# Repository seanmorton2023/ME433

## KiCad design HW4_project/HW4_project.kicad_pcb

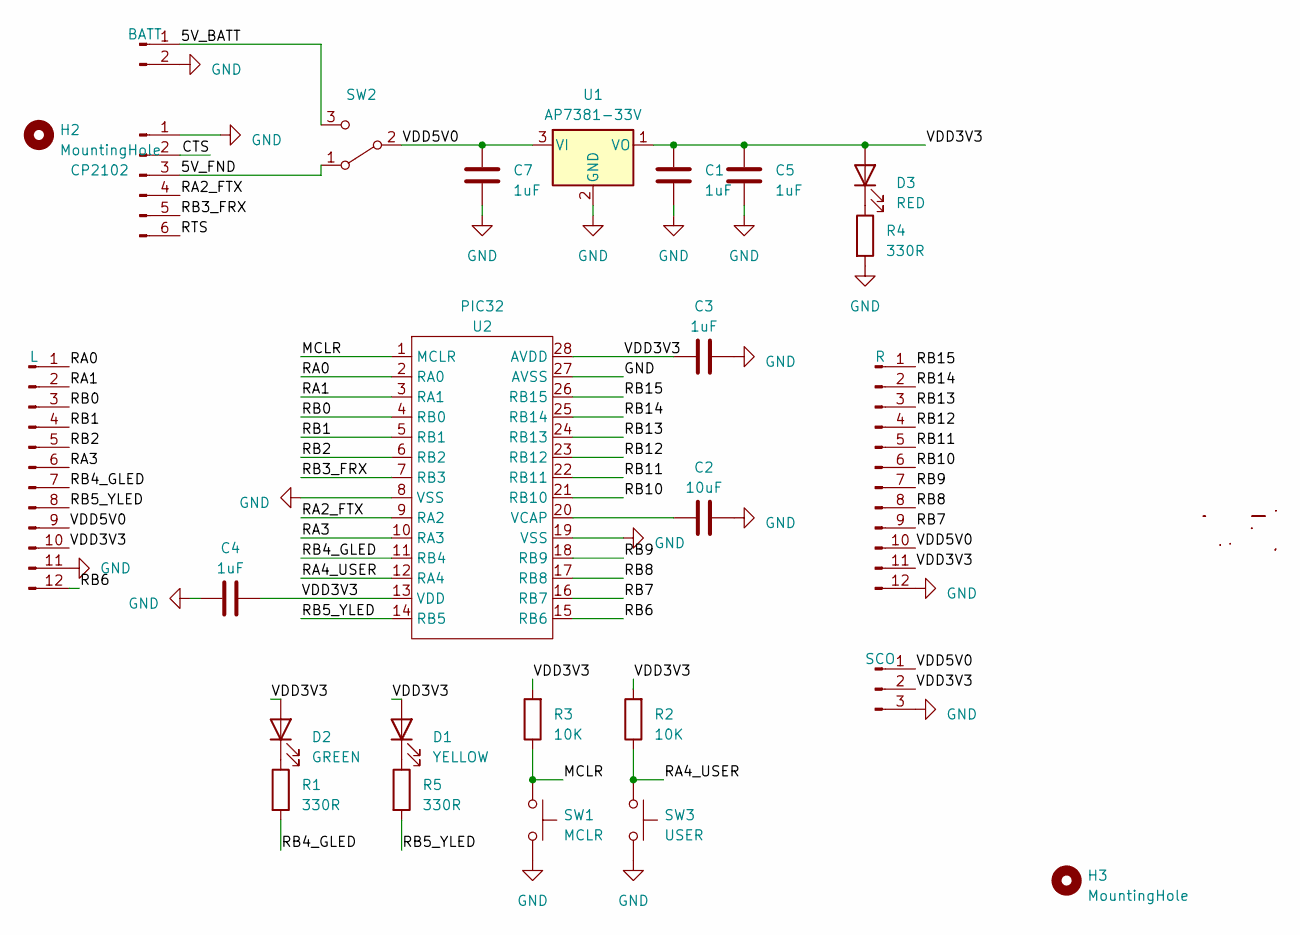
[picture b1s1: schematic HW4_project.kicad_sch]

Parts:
C1, C3, C4, C5, C7: 1uF; C_Disc_D4.3mm_W1.9mm_P5.00mm
C2: 10uF; C_Disc_D3.4mm_W2.1mm_P2.50mm
D1: YELLOW; LED_D4.0mm
D2: GREEN; LED_D4.0mm
D3: RED; LED_D4.0mm
H2, H3: MountingHole; MountingHole_3.2mm_M3_Pad
J1: CP2102; PinHeader_1x06_P2.54mm_Vertical
J2: BATT; PinHeader_1x02_P2.54mm_Vertical
J3: L; PinHeader_1x12_P2.54mm_Vertical
J4: R; PinHeader_1x12_P2.54mm_Vertical
J5: SCO; PinHeader_1x03_P2.54mm_Vertical
R1, R4, R5: 330R; R_Axial_DIN0207_L6.3mm_D2.5mm_P7.62mm_Horizontal
R2, R3: 10K; R_Axial_DIN0207_L6.3mm_D2.5mm_P7.62mm_Horizontal
SW1: MCLR; BTN_2pin_square
SW2: SW_SPDT; EG1218 switch
SW3: USER; BTN_2pin_square
U1: AP7381-33V; TO-92_Inline_Wide
U2: PIC32; DIP-28_W7.62mm_Socket_LongPads

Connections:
/5V_BATT: J2.1, SW2.3 (C)
/5V_FND: J1.3, SW2.1 (A)
/CTS: J1.2
/MCLR: R3.1, SW1.1, U2.1 (MCLR)
/RA0: J3.1, U2.2 (RA0)
/RA1: J3.2, U2.3 (RA1)
/RA2_FTX: J1.4, U2.9 (RA2)
/RA3: J3.6, U2.10 (RA3)
/RA4_USER: R2.1, SW3.1, U2.12 (RA4)
/RB0: J3.3, U2.4 (RB0)
/RB1: J3.4, U2.5 (RB1)
/RB2: J3.5, U2.6 (RB2)
/RB3_FRX: J1.5, U2.7 (RB3)
/RB4_GLED: J3.7, R1.2, U2.11 (RB4)
/RB5_YLED: J3.8, R5.2, U2.14 (RB5)
/RB6: J3.12, U2.15 (RB6)
/RB7: J4.9, U2.16 (RB7)
/RB8: J4.8, U2.17 (RB8)
/RB9: J4.7, U2.18 (RB9)
/RB10: J4.6, U2.21 (RB10)
/RB11: J4.5, U2.22 (RB11)
/RB12: J4.4, U2.23 (RB12)
/RB13: J4.3, U2.24 (RB13)
/RB14: J4.2, U2.25 (RB14)
/RB15: J4.1, U2.26 (RB15)
/RTS: J1.6
/VDD3V3: C1.1, C3.1, C4.2, C5.1, D1.2 (A), D2.2 (A), D3.2 (A), J3.10, J4.11, J5.2, R2.2, R3.2, U1.1 (VO), U2.13 (VDD), U2.28 (AVDD)
/VDD5V0: C7.1, J3.9, J4.10, J5.1, SW2.2 (B), U1.3 (VI)
GND: C1.2, C2.2, C3.2, C4.1, C5.2, C7.2, H2.1, H3.1, J1.1, J2.2, J3.11, J4.12, J5.3, R4.2, SW1.2, SW3.2, U1.2 (GND), U2.8 (VSS), U2.19 (VSS), U2.27 (AVSS)
unnamed: D1.1 (K), R5.1
unnamed: D2.1 (K), R1.1
unnamed: D3.1 (K), R4.1
unnamed: C2.1, U2.20 (VCAP)

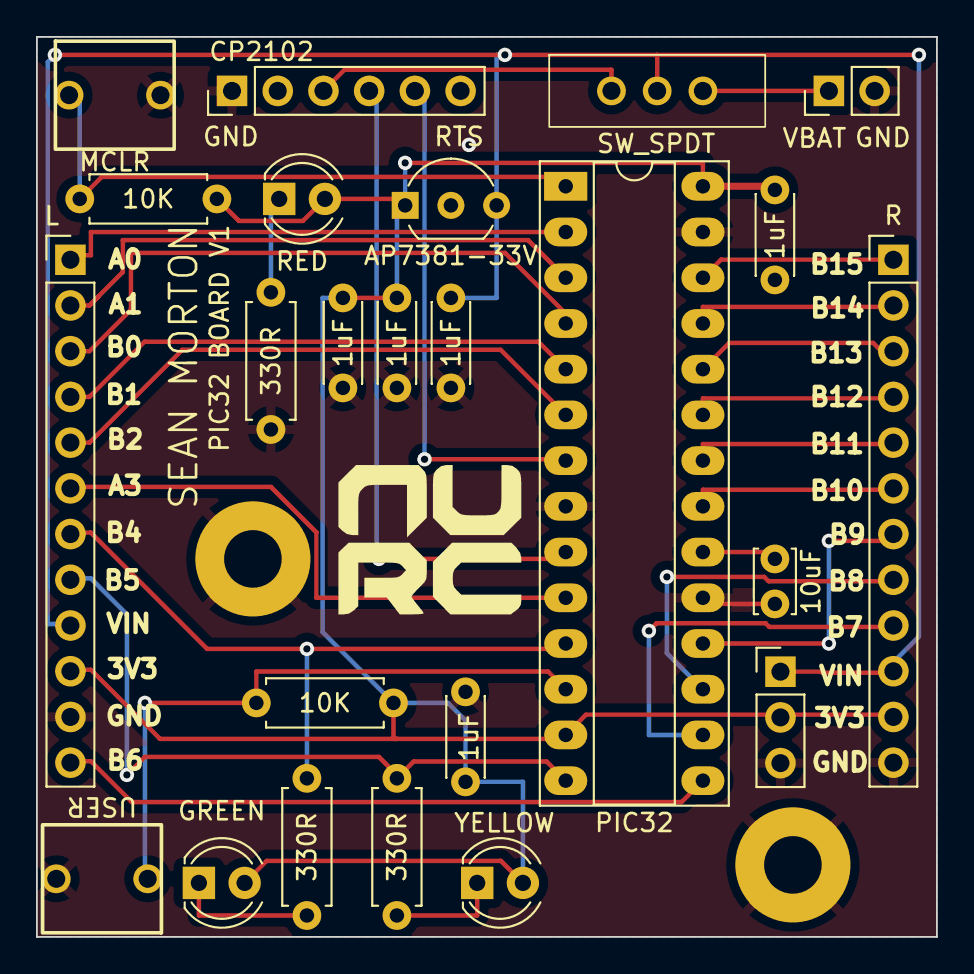
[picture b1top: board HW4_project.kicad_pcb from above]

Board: 2 copper layers, 50.0 x 50.0 mm, 26 parts (0 on the bottom side), 31 nets.

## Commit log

2023-04-01 HW2: started sample project
2023-04-04 HW2 submission
    pics and videos are under hw2.x/media
2023-04-04 HW2 media
    ...since it's in the requirements for this class, it's gonna be in the repo. except videos - those get submitted to Canvas
2023-04-06 HW3: added code
    code currently sends 1 sine wave every time button is pressed; viewed it on Arduino serial plotter
2023-04-06 HW3 submission
    successfully plots a sine wave of amplitude 1.65V and midpoint 1.65V
2023-04-13 HW4 + HW5 init
    - make first draft of PCB design for HW4
    - initialized HW5 project
2023-04-16 HW5: added files
    started work on the SPI DAC code
2023-04-16 HW5: 1st draft code
    covers all the bases, but is untested. test a little bit at a time
2023-04-19 Created HW6; edited HW5
    changed HW5 SPI initialization functions to choose pins for SDO, SDI, CS
2023-04-19 file organization
2023-04-20 init HW7; add HW6 I2C; modify HW5
    see Sarah's format for how she did a triangle wave in this commit
2023-04-20 HW5: sin and tri waves work
    had to fix bit-shifting and redefine my triangle wave, but both show up pretty clearly at low freqs. next up is to have both show up on the 2 output channels
2023-04-20 HW5 submission
    fixed SPI baud rate; signal now shows clean triangle and sine waves at the right frequencies
2023-04-25 HW6: got I2C writes working
    had a bad line of code where I was sending a start bit instead of a stop bit
2023-04-25 HW6: got I2C reads working
    - don't need to specify a register that we're reading from during the "read" cmd; the previous "write" specifies that
    - added a stop bit before the restart bit - Marchuk says "restart" bit is the same as the "start" bit
    - changed ACK to NACK to specify we don't need to read any more bytes from the IO expander
2023-04-25 HW6 submission
2023-04-25 HW7 submission
2023-04-25 undo HW6 template.c change
    from HW7 submission
2023-04-25 initialized HW8
2023-04-26 HW8: writing strings to screen works
2023-04-26 HW8 submission
    takes the acceleration from the MPU6050 and prints it to the SSD1306 display
2023-04-29 initialized HW9
2023-05-03 HW9: start on FFT
    didn't seem economical to spend too much more time on it
2023-05-03 HW9: modularized FFT code
    plus made a main function
2023-05-03 HW9: moving average
    works pretty well; still need to do the IIR and FIR
2023-05-03 HW9: IIR
    plus improvements to plotting
2023-05-11 HW9: attempted FIR
    was going to have the signal come in one element at a time, convolve it, and use the plotting animation to show it changing in time. decided after that this wouldn't be any better than just showing t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
    attempting that method now; this version remains for the sake of bookkeeping
2023-05-13 HW9: FIR working
    should have pushed earlier, but: I've used np.convolve() and plotted the middle n datapoints versus the original signal
    code is broken because I'm reorganizing the way we plot
2023-05-13 HW9: DSP refined
    modular code and fancy Python programming lesgooooo
2023-05-13 HW9 submission
2023-05-16 HW10 init; draft of setColor
    broke down setColor lines into process_color() and append_to_delay_times() for the sake of ease. everything outside of the "loop through WS2812B" within setColor was part of the default code
2023-05-16 HW10: main() structure
2023-05-16 HW11: init; wrote key functions
    broke apart code into a client and a microcontroller - microcontroller sends data over Serial to be plotted to the client
2023-05-16 HW11: receiving data over serial
    it's kinda scuffed with Pico, but I found a way to send and receive the data arrays
2023-05-16 HW11 submission
    client now receives the data and makes pretty plots!
2023-05-16 HW10: mostly works!
    had a spare LATBINV in my code that inverted pin B6, not B0 - solving that helped. I also had to change a bitwise | to a bitwise & to interpret one bit at a time
    unresolved: first LED is changing colors on a different cycle from others
2023-05-16 HW10 submission
    shows a changing array of RGB LEDs with a different color cycle per LED
2023-05-25 HW4: silkscreen revisions
    - added labels for all the broken-out pins
    - fixed spacing on the button components
    - added NURC logo
2023-05-25 HW13: initial commit
    note: two versions of the website code exist; v1 was written by Marchuk, v2 was written by Andre
2023-05-25 HW4 submission
    - revised label for battery input voltage
    - revised routing of 2 traces
    - generated STEP file for robot modeling
2023-05-26 HW13: web server working
    adafruit made some big changes to the way their Server class works, including:
    - class names don't start with "HTTP" anymore
    - Method class has been removed; now method is a positional argument of the @server.route() function and uses plain text
    - Requests work way different; needs to return a Response object like this: return Response(request, body=body, content_type="text/HTML")
2023-05-26 HW13 submission
    ended up sticking with the Javascript method for button-press event handlers from template #1
2023-05-29 HW12 submission
    just pics of CAD. model is stored at the link below (not public at the time of this commit)
    https://cad.onshape.com/documents/54900c11b64ff2b40b1e8b55/w/4fca28bb05f32ea6f30522d4/e/44874b33dba2b4eb3e83cb46
2023-06-07 HW14: initial commit
2023-06-07 HW14: PWM.h
    need to update the PR to be as large as possible, but the structure exists
2023-06-08 HW14: first draft of code
    added servo.c as a library for the servo
2023-06-08 HW14: tested limits of servo's motion
    given PR2 = 60000: OC1RS = 1200 and 6200 were the 0deg and 180 marks
2023-06-08 HW15: added files
    this HW is optional, but I wanted to see how much time it'd take to get working
2023-06-08 HW14 submission
